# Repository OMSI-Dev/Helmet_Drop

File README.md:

# Helmet  Electronics Details
## Theory of Operation
The basic gameplay is to open a sliding door, add cushioning materials, close the door and a ‘hammer’ drops to update data on a monitor. An accelerometer is attached to the center of the falling ‘hammer.’ During the fall acceleration & deceleration is recorded to an array and sent to the processing app via serial. Processing parses the data and plots it to the graph. Based on success levels processing will update images, colors, and play a sound. 

Processing controls the timing for the gameplay while the uController waits to receive signals via serial. The uController has several sensors to ensure safety and proper alignment. To sense the door’s close/open state it uses both a reed (NO) & a button trigger(NO). The reed confirms if the door has been reopened allowing for the next attempt.  

Once the door is closed a maglock engages preventing the door to be opened during the hammer drop. Indicating LEDs show if the lock is engaged or not. During startup the uController uses an IR sensor to find the ‘home’ location of the hammer. This is done to ensure repeatability and easy setup. 

## Updating software

The software is built using platform.io. You can use Arduino IDE by copying the src folder and renaming it to Helmet and renaming the main.cpp file to ‘Helmet.ino’. This will allow you to use Arduino to make modifications. You will need to install any missing libraries through the Arduino Library manager.

## Project File Organization

	docs : documentation and pictures
	src : source code
	eagle : pcb files
	examples_tests : N/A
	processing: location of computer app
	processing/data: assets used for the processing app
	readme.md : basic project info its the file you are reading
	resources:Helmet_Drop BOM.xls
	
	some other directories are used by platformio and vscode

#### Hardware

**Phoenix connectors:**

2-pin: (4 qty)

	1. 24V
	2. Safety Switch
	3. Accel Sensor (1 pair)
	
3-pin: (3 qty)

	1. IR In
	2. Reed In
	3. 12v In
	
4-pin: (2 qty)

	1. Stepper Motor
	2. Maglock
	
6-pin: (1 qty)

	1.Lock Light
	2.Unlock Light

Various Components:

	3 mosfets (SMD 7460AAW44K)
	3 10K SMS Resistors
	32U4 - 5v itsyBitsy
	Stepper Motor
	Stepper Driver
	IR Sensor (CPB765WZ)
	Happ Switch
	Reed Switch
	Maglock
	24V PSU
	12V PSU
	5V across USB

#### Sensor Board
IR sensor board - used to set IR with resistors as well as a troubleshooting board.

## Audio
They are Mp3 files stored /data/sound/ and can be updated simply by following the naming scheme and replacing old files. It is recommended making a backup before replacing any files. 
Capitalization matters. 

##### Naming scheme:

	Failure: red.mp3
	Average: orange.mp3
	Success: green.mp3

## Images/video

The images are saved as PNG and the video is MP4, both are stored /data/images.  by following the naming scheme and replacing old files. It is recommended making a backup before replacing any files. Capitalization matters. 

##### Naming scheme:

	Arrow Failure: redArrow.gif
	Arrow Average: yellowArrow.gif
	Arrow Success: greenArrow.gif
	Head Failure: 3_en.png
	Head Average:  2_en.png
	Head Success:  1_en.png
	Video: attractor.mp4

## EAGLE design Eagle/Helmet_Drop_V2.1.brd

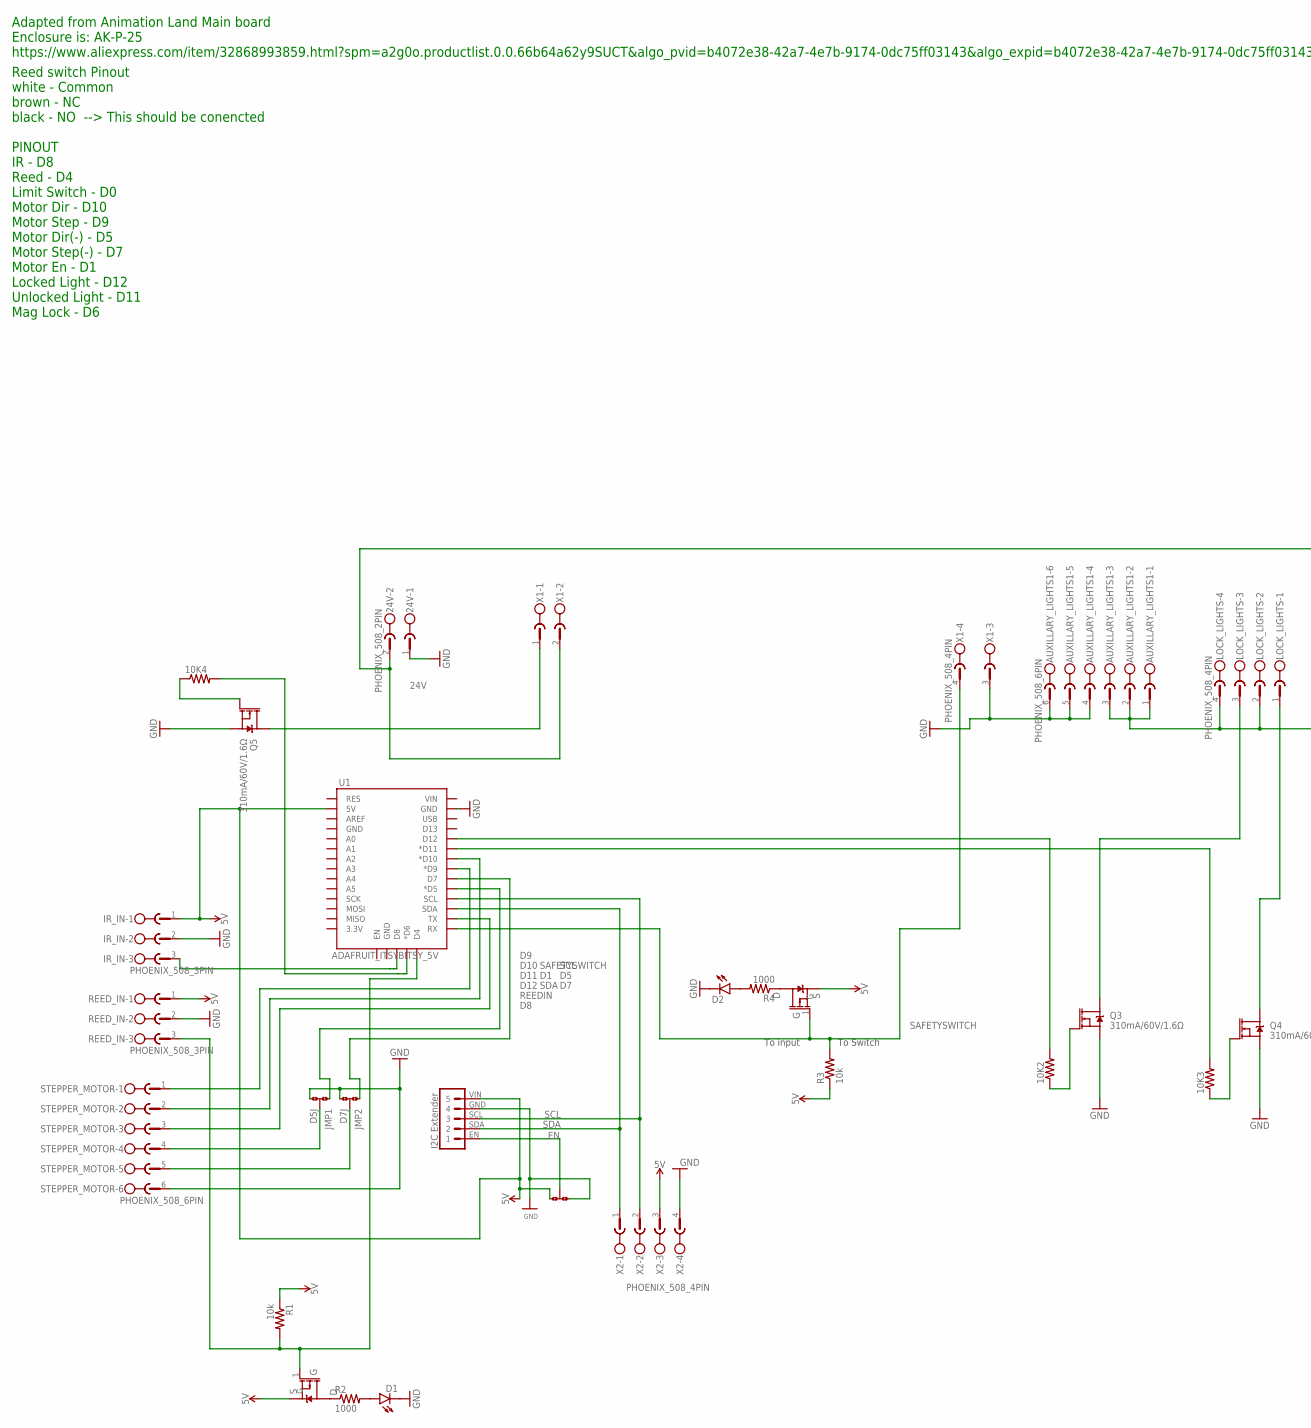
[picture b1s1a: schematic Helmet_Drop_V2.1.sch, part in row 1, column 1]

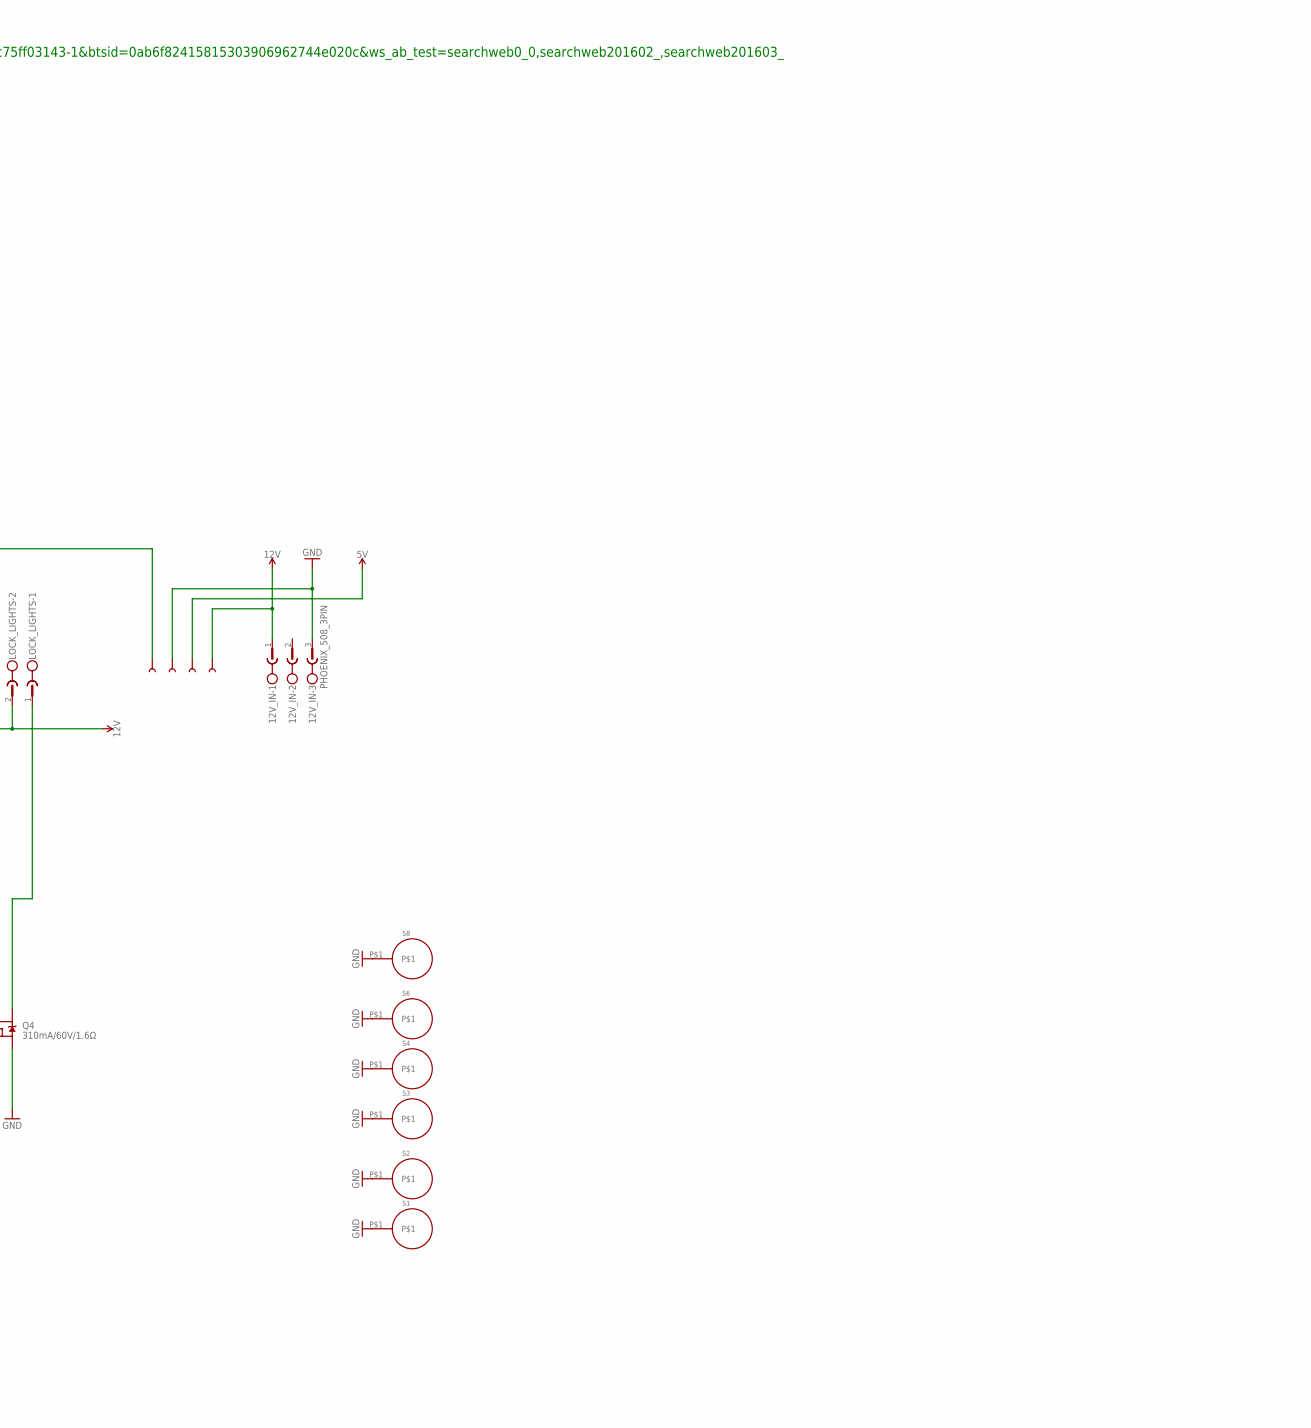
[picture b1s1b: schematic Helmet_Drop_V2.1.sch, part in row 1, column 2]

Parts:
10K2, 10K3, 10K4: RESISTORS0805-RES; SMD_RESISTOR_0805
12V_IN: PHOENIX_508_3PIN
24V: PHOENIX_508_2PIN
AUXILLARY_LIGHTS1: PHOENIX_508_6PIN
D1, D2: GENERIC_LED1206; SMD_LED-1206
IR_IN: PHOENIX_508_3PIN
JMP1, JMP2, JMP3: SMD_JUMPERA; JUMPER_A-OR
LOCK_LIGHTS: PHOENIX_508_4PIN
Q1, Q2: MOSFET-PCHIRLML9301TRPBF; SOT23-3
Q3, Q4, Q5: 310mA/60V/1.6Ω; SO-8_POWER_PAK
R1, R3: 10k; SMD_RESISTOR_0805
R2, R4: 1000; SMD_RESISTOR_0805
REED_IN: PHOENIX_508_3PIN
S1, S2, S3, S4, S6, S8: GND_HOLE
STEPPER_MOTOR: PHOENIX_508_6PIN
TP1, TP2, TP3, TP4: TEST_POINTTP_15TH_THRU; TESTPOINT_HEADER_1X01
U1: ADAFRUIT_ITSYBITSY_5V; ADAFRUIT_ITSYBITSY
U$1: I2C_EXTENDER
X1, X2: PHOENIX_508_4PIN

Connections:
5V: IR_IN.1, JMP3.1, Q1.2 (S), Q2.2 (S), R1.1, R3.1, REED_IN.1, TP3.P$1, U1.5V, U$1.VIN (5), X2.3
12V: 12V_IN.1, AUXILLARY_LIGHTS1.1, AUXILLARY_LIGHTS1.2, AUXILLARY_LIGHTS1.3, LOCK_LIGHTS.2, LOCK_LIGHTS.4, TP4.P$1
24V: 24V.2, TP1.P$1, X1.2
D1: STEPPER_MOTOR.3, U1.TX
D5: JMP1.1, U1.D5 (*D5)
D5J: JMP1.2, STEPPER_MOTOR.4
D7: JMP2.1, U1.D7
D7J: JMP2.2, STEPPER_MOTOR.5
D8: IR_IN.3, U1.D8
D9: STEPPER_MOTOR.1, U1.D9 (*D9)
D10: STEPPER_MOTOR.2, U1.D10 (*D10)
D11: 10K3.2, U1.D11 (*D11)
D12: 10K2.2, U1.D12
EN: JMP3.2, U$1.EN (1)
GND: 12V_IN.3, 24V.1, AUXILLARY_LIGHTS1.4, AUXILLARY_LIGHTS1.5, AUXILLARY_LIGHTS1.6, D1.C, D2.C, IR_IN.2, JMP1.3, JMP2.3, JMP3.3, Q3.S, Q4.S, Q5.S, REED_IN.2, S1.P$1, S2.P$1, S3.P$1, S4.P$1, S6.P$1, S8.P$1, STEPPER_MOTOR.6, TP2.P$1, U1.GND@2 (GND), U$1.GND (4), X1.3, X2.4
unnamed: 10K4.2, U1.D6 (*D6)
unnamed: Q1.3 (D), R4.1
unnamed: D2.A, R4.2
unnamed: Q2.3 (D), R2.1
unnamed: D1.A, R2.2
unnamed: LOCK_LIGHTS.3, Q3.D1 (D)
unnamed: LOCK_LIGHTS.1, Q4.D1 (D)
unnamed: 10K2.1, Q3.G
unnamed: Q5.D1 (D), X1.1
unnamed: 10K3.1, Q4.G
unnamed: 10K4.1, Q5.G
REEDIN: Q2.1 (G), R1.2, REED_IN.3, U1.D4
SAFETYSWITCH: Q1.1 (G), R3.2, U1.RX, X1.4
SCL: U1.SCL, U$1.SCL (3), X2.2
SDA: U1.SDA, U$1.SDA (2), X2.1

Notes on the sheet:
Adapted from Animation Land Main board Enclosure is: AK-P-25 https://www.aliexpress.com/item/32868993859.html?spm=a2g0o.productlist.0.0.66b64a62y9SUCT&algo_pvid=b4072e38-42a7-4e7b-9174-0dc75ff03143&algo_expid=b4072e38-42a7-4e7b-9174-0dc75ff03143-1&btsid=0ab6f82415815303906962744e020c&ws_ab_test=sea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
Reed switch Pinout white - Common brown - NC black - NO --> This should be conencted PINOUT IR - D8 Reed - D4 Limit Switch - D0 Motor Dir - D10 Motor Step - D9 Motor Dir(-) - D5 Motor Step(-) - D7 Motor En - D1 Locked Light - D12 Unlocked Light - D11 Mag Lock - D6
To Switch
To input

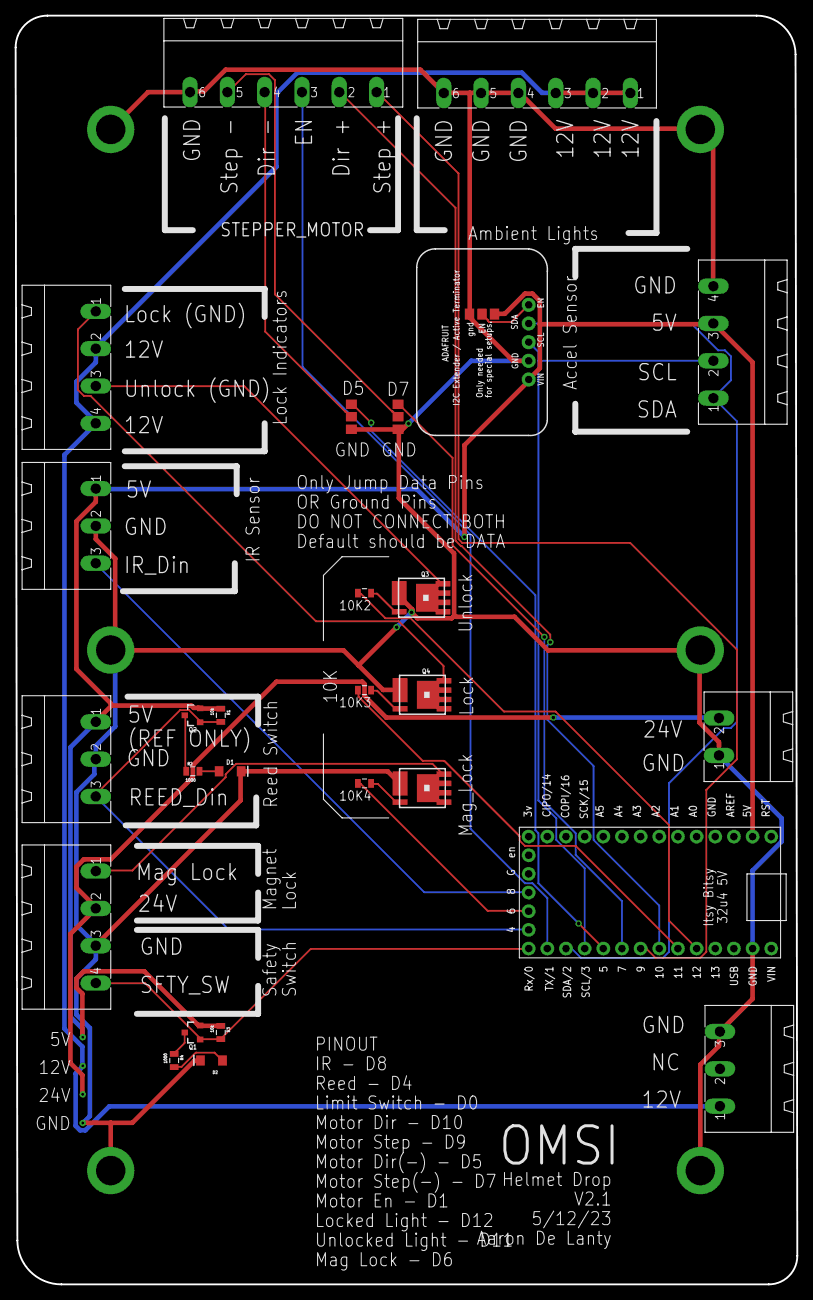
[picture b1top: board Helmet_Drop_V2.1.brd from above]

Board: 2 copper layers, 106.4 x 172.7 mm, 38 parts (0 on the bottom side), 30 nets.

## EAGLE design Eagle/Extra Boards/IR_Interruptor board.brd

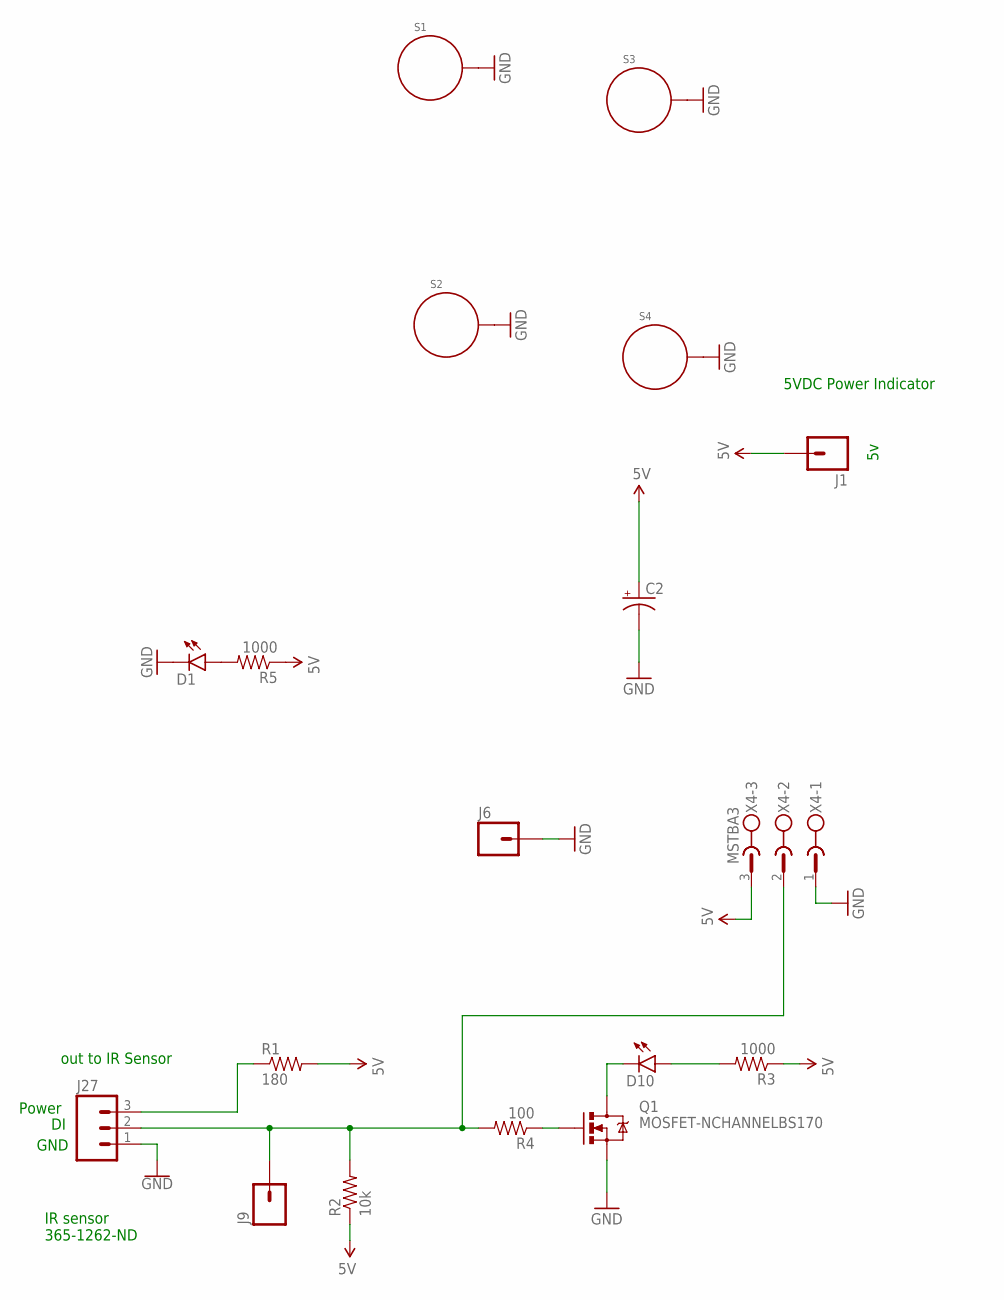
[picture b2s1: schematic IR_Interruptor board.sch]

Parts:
C2: CAP_POLPTH2; CPOL-RADIAL-10UF-25V
D1, D10: LED1206; LED-1206
J1, J6, J9: M01PTH; 1X01
J27: M03SCREW; SCREWTERMINAL-3.5MM-3
Q1: MOSFET-NCHANNELBS170; TO-92
R1: 180; 0805
R2: 10k; 0805
R3, R5: 1000; 0805
R4: 100; 0805
S1, S2, S3, S4: STANDOFF_ELECTRICAL; STANDOFF-ELECTRICAL
X4: MSTBA3

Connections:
5V: C2.1 (+), J1.1, R1.2, R2.1, R3.1, R5.1, X4.3
DO: J9.1, J27.2, R2.2, R4.2, X4.2
GND: C2.2 (-), D1.C, J6.1, J27.1, Q1.3 (S), S1.P1, S2.P1, S3.P1, S4.P1, X4.1
unnamed: Q1.2 (G), R4.1
unnamed: D10.C, Q1.1 (D)
unnamed: D1.A, R5.2
unnamed: D10.A, R3.2
POWER: J27.3, R1.1

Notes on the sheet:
5VDC Power Indicator
IR sensor 365-1262-ND
out to IR Sensor
GND
Power

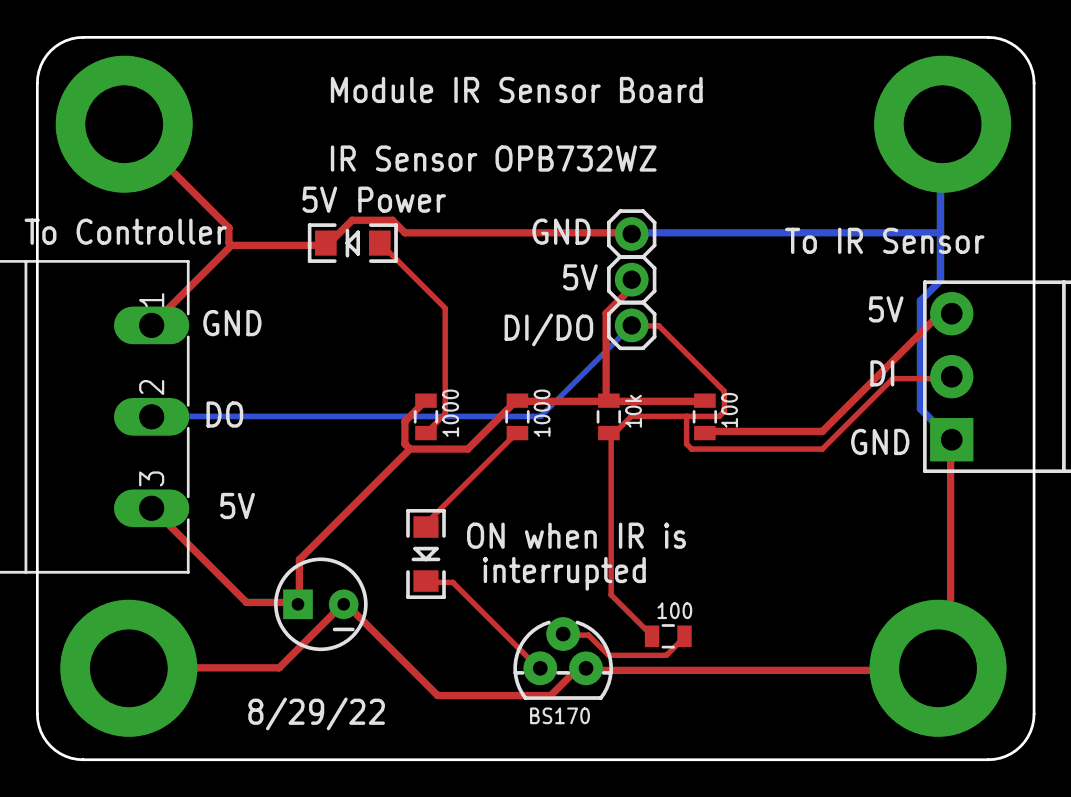
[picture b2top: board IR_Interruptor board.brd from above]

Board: 2 copper layers, 55.4 x 40.1 mm, 18 parts (0 on the bottom side), 8 nets.

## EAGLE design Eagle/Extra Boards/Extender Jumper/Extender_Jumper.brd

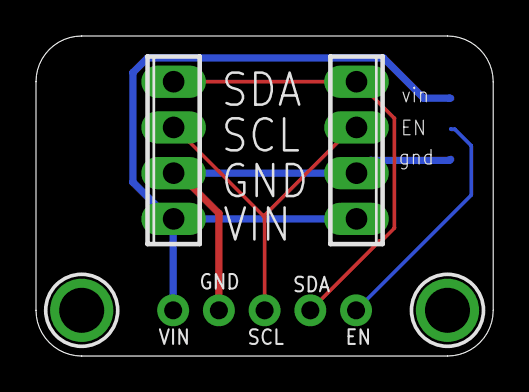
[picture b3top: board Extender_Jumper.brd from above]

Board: 2 copper layers, 25.4 x 17.8 mm, 6 parts (1 on the bottom side), 5 nets.

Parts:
JMP1: 0R-JUMPA; A0R-JMP
JP2: 1X05_ROUND_70
U$19, U$21: MOUNTINGHOLE2.5; MOUNTINGHOLE_2.5_PLATED
X1, X2: 4POL254

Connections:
EN: JMP1.2, JP2.5
GND: JMP1.3, JP2.2, X1.2, X2.3
SCL: JP2.3, X1.3, X2.2
SDA: JP2.4, X1.4, X2.1
VCC: JMP1.1, JP2.1, X1.1, X2.4

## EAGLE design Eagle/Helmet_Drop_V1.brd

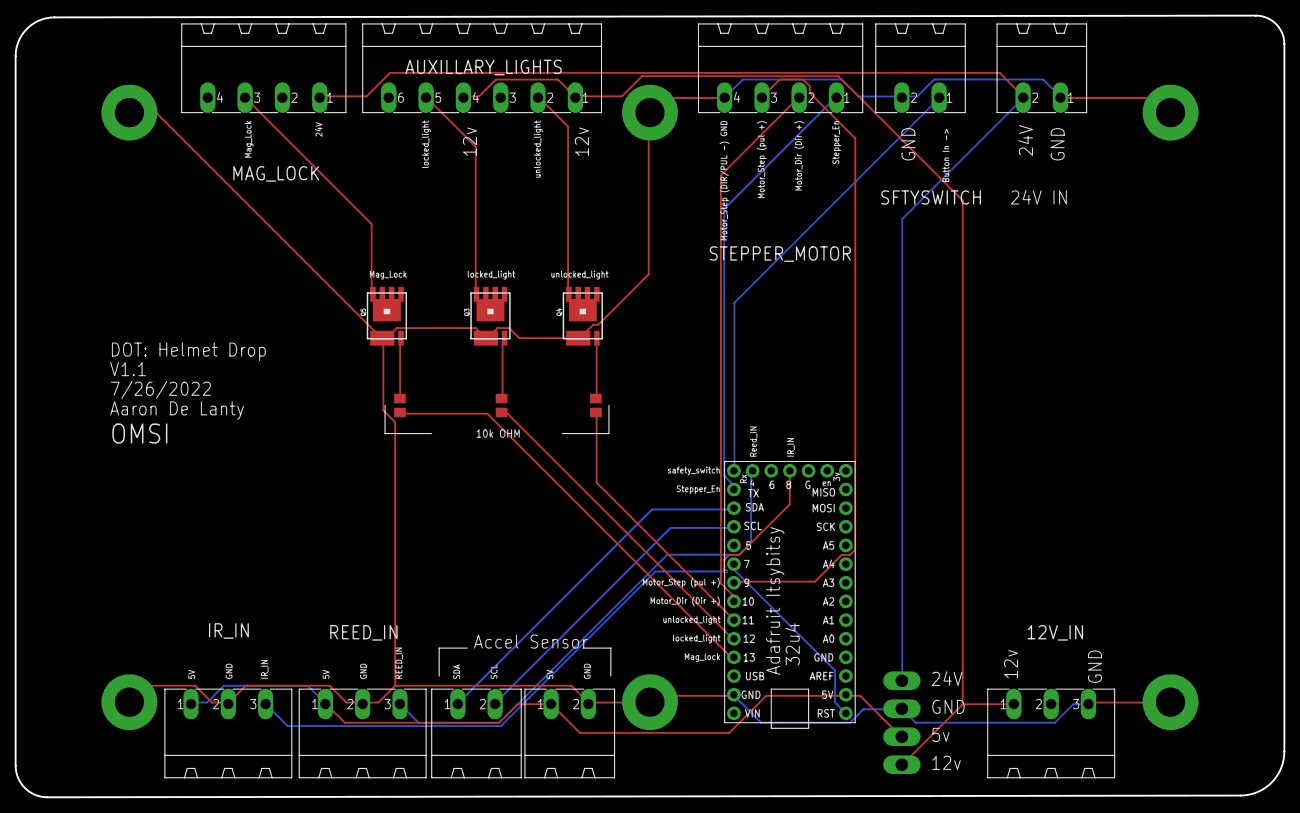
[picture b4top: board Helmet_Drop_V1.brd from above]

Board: 2 copper layers, 172.7 x 106.4 mm, 25 parts (0 on the bottom side), 22 nets.

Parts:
5V_IN, 24V: MSTBA2
10K2, 10K3, 10K4: M0805
12V_IN: MSTBA3
AUXILLARY_LIGHTS: MSTBA6
IR_IN: MSTBA3
MAG_LOCK: MSTBA4
Q3, Q4, Q5: MOSFET-NCH; SO-8_POWER_PAK
REED_IN: MSTBA3
S1, S2, S3, S4, S6, S8: STANDOFF_ELECTRICAL5-32; STANDOFF_ELECTRICAL_5_32
SDA_SCL: MSTBA2
SFTYSWITCH: MSTBA2
STEPPER_MOTOR: MSTBA4
TP1, TP2: PTR2; P2-38-17
U1: ITSYBITSY_5V; ADAFRUIT_LENOARDO

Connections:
5V: 5V_IN.1, IR_IN.1, REED_IN.1, TP2.TP-1, U1.5V
12V: 12V_IN.1, AUXILLARY_LIGHTS.1, AUXILLARY_LIGHTS.4, TP2.TP-2
GND: 5V_IN.2, 12V_IN.3, 24V.1, IR_IN.2, Q3.S, Q4.S, Q5.S, REED_IN.2, S1.P1, S2.P1, S3.P1, S4.P1, S6.P1, S8.P1, SFTYSWITCH.2, STEPPER_MOTOR.4, TP1.TP-2, U1.GND@2
unnamed: 10K4.2, U1.D13
unnamed: SFTYSWITCH.1, U1.RX
unnamed: STEPPER_MOTOR.3, U1.D9
unnamed: U1.D7, U1.RES
unnamed: STEPPER_MOTOR.2, U1.D10
unnamed: AUXILLARY_LIGHTS.5, Q3.D1
unnamed: STEPPER_MOTOR.1, U1.TX
unnamed: 10K2.1, Q3.G
unnamed: REED_IN.3, U1.D4
unnamed: IR_IN.3, U1.D8
unnamed: SDA_SCL.1, U1.SDA
unnamed: SDA_SCL.2, U1.SCL
unnamed: 10K2.2, U1.D12
unnamed: MAG_LOCK.3, Q5.D1
unnamed: 24V.2, MAG_LOCK.1, TP1.TP-1
unnamed: AUXILLARY_LIGHTS.2, Q4.D1
unnamed: 10K3.2, U1.D11
unnamed: 10K3.1, Q4.G
unnamed: 10K4.1, Q5.G

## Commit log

2022-09-12 init
2022-09-12 added image assests
2022-09-12 documentation
2022-09-19 Create Helmet
2022-09-19 Updated CAM for circuit manufacturing
2022-09-23 various fixes
2022-11-16 Updated to make newest repository location
2023-01-07 updated homing and pins
2023-01-18 adjusted image limits & data
2023-02-03 test update
2023-02-16 added drift correction & door catch
2023-02-16 fixed bool & added double check for safety
2023-02-20 added in Serial timeout
2023-03-29 Door Safty Update
2023-03-29 reduced chart values
2023-03-29 Added logFile generation
2023-04-03 Update Helmet_drop.pde
    This should correct errors when applying to the graph. Generates a logFile. If fails 2nd attempt to update it will close the program and update the log.
2023-04-06 Exit Code Added & Eased Difficulty
2023-05-16 Moved connectors for ease of access
2023-05-19 Logs from testing
2023-06-22 board fix
2023-07-19 added try-catch to accel read
2023-07-20 e-homing switch added
2023-08-25 studpid hammer update
2023-09-18 update 5V lead and comments
2023-10-06 updated indicator lights
2023-10-09 cleanup

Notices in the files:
parts and their libraries:
microbuilder: This work is placed in the public domain, and may be freely used for commercial and non-commercial work with the following conditions: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
SparkFun-Connectors: Licensing: CC v3.0 Share-Alike You are welcome to use this library for commercial purposes.
